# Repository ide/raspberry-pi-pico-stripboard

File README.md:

# Raspberry Pi Pico Stripboard

A stripboard PCB designed for the Raspberry Pi Pico. Compatible with Pico W also.

## Features

- Neatly sized to fit the Pico family of boards
- Reversible design—flip it any way you need
- Large ground plane

## Purpose

Use this stripboard to permanently solder through-hole components to a Raspberry Pi Pico, designed for tidy, complete projects that don't need a custom PCB. Unlike protoboards, the footprint of this stripboard matches the Pico's within a couple tenths of a millimeter.

The stripboard has a breadboard-like layout of horizontal rows of holes connected to each other. Both the left and right sides have four holes per row, each. This allows up to three components to be soldered to each pin of the Pico. The rows connected to ground are an exception. Because the Pico's ground pins are mirrored on the left and right sides, the rows connected to ground are connected all the way across the stripboard.

Aside from the ground rows, the traces between holes in the same row can be drilled or scratched out to separate the holes if needed.

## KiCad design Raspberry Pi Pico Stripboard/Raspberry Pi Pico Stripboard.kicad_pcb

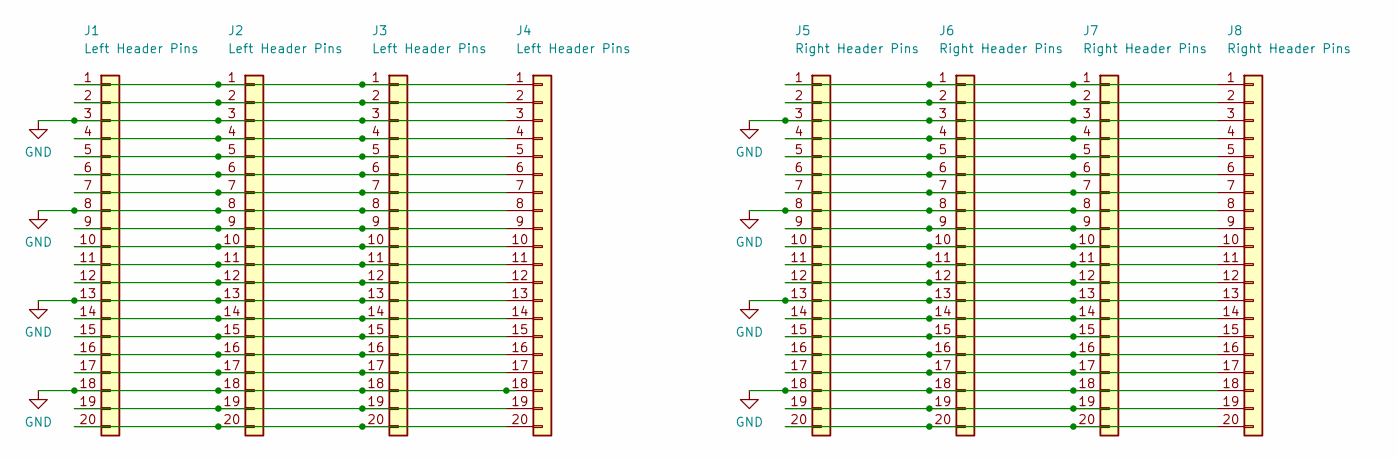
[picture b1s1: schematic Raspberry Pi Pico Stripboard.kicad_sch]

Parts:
J1, J2, J3, J4: Left Header Pins; PinHeader_1x20_P2.54mm_Vertical_Uniform
J5, J6, J7, J8: Right Header Pins; PinHeader_1x20_P2.54mm_Vertical_Uniform

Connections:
GND: J1.3, J1.8, J1.13, J1.18, J2.3, J2.8, J2.13, J2.18, J3.3, J3.8, J3.13, J3.18, J4.3, J4.8, J4.13, J4.18, J5.3, J5.8, J5.13, J5.18, J6.3, J6.8, J6.13, J6.18, J7.3, J7.8, J7.13, J7.18, J8.3, J8.8, J8.13, J8.18
unnamed: J1.1, J2.1, J3.1, J4.1
unnamed: J1.2, J2.2, J3.2, J4.2
unnamed: J1.4, J2.4, J3.4, J4.4
unnamed: J1.5, J2.5, J3.5, J4.5
unnamed: J1.6, J2.6, J3.6, J4.6
unnamed: J1.7, J2.7, J3.7, J4.7
unnamed: J1.9, J2.9, J3.9, J4.9
unnamed: J1.10, J2.10, J3.10, J4.10
unnamed: J1.11, J2.11, J3.11, J4.11
unnamed: J1.12, J2.12, J3.12, J4.12
unnamed: J1.14, J2.14, J3.14, J4.14
unnamed: J1.15, J2.15, J3.15, J4.15
unnamed: J1.16, J2.16, J3.16, J4.16
unnamed: J1.17, J2.17, J3.17, J4.17
unnamed: J1.19, J2.19, J3.19, J4.19
unnamed: J1.20, J2.20, J3.20, J4.20
unnamed: J5.1, J6.1, J7.1, J8.1
unnamed: J5.2, J6.2, J7.2, J8.2
unnamed: J5.4, J6.4, J7.4, J8.4
unnamed: J5.5, J6.5, J7.5, J8.5
unnamed: J5.6, J6.6, J7.6, J8.6
unnamed: J5.7, J6.7, J7.7, J8.7
unnamed: J5.9, J6.9, J7.9, J8.9
unnamed: J5.10, J6.10, J7.10, J8.10
unnamed: J5.11, J6.11, J7.11, J8.11
unnamed: J5.12, J6.12, J7.12, J8.12
unnamed: J5.14, J6.14, J7.14, J8.14
unnamed: J5.15, J6.15, J7.15, J8.15
unnamed: J5.16, J6.16, J7.16, J8.16
unnamed: J5.17, J6.17, J7.17, J8.17
unnamed: J5.19, J6.19, J7.19, J8.19
unnamed: J5.20, J6.20, J7.20, J8.20

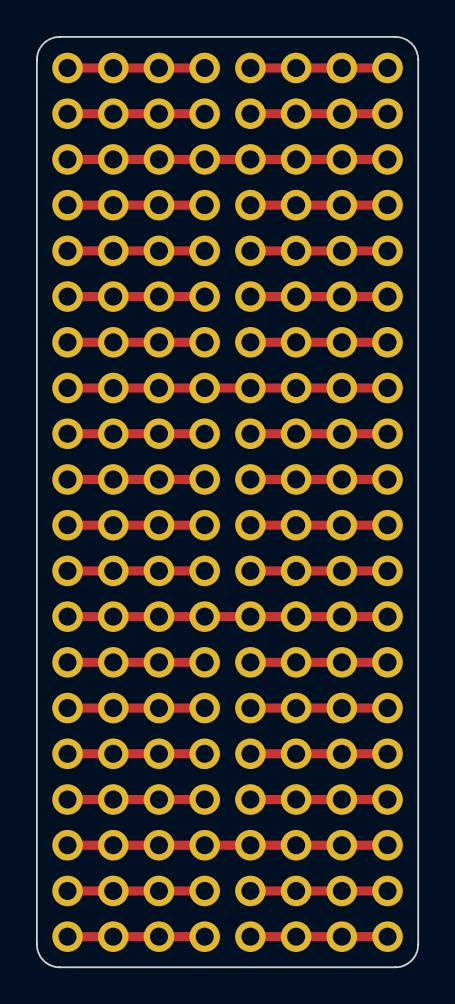
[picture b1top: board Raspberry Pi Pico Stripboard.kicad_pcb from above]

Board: 2 copper layers, 21.2 x 51.7 mm, 8 parts (0 on the bottom side), 33 nets.

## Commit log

2022-11-01 README, schematics, PCB design
